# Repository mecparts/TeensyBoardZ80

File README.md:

# Teensy Board/Z80 - A Teensy4.0 based ZCPR3.3/ZSDOS Z80 computer

The Teensy Board/Z80 is a
[Teensy 4.0](https://www.pjrc.com/store/teensy40.html) computer running a
ZCPR3.3/ZSDOS variant of [RunCPM](https://github.com/MockbaTheBorg/RunCPM).

Features:
* 100-140MHz equivalent Z80 (RunCPM doesn't emulate cycle times - it just goes *fast*).
* SDIO connected uSD card (about 2.5x faster than SPI) with a standard FAT file system.
* ANSI colour terminal emulator with [GSX](https://github.com/mecparts/pigfx)
graphics support. Runs on a first generation Raspberry Pi, so HDMI video
and USB keyboards are natively supported.
* Battery backed up real time clock.
* Centronics compatible parallel port (DB-25F).
* RS-232 serial port (DE-9M) with RTS/CTS hardware flow control.

## Hardware

The PCB for the Teensy Board/Z80 fits on a VESA mount along with an
original Raspberry Pi 1 B (rev 2). The Pi is the ANSI console used by
the Teensy Board/Z80.

Along with the internal connection to the ANSI terminal, the Teensy Board/Z80
has two vintage I/O ports: an RS-232 port with a DE-9 connector, with
RTS/CTS handshaking, and a Centronics parallel port. The RS-232 port is
the TTY: device in the Teensy Board/Z80's BIOS. The parallel port is,
quite naturally, the LPT: device.

In my setup, the RS-232 port is hooked up to a
[Retro WiFi modem](https://github.com/mecparts/RetroWiFiModem), complete
with Hayes Smartmodem style LED indicators.

The Teensy 4's real time clock is used in ZSDOS to support file timestamps
via the normal ZSDOS calls. A CR2032 coin cell provides the battery back up.

## Case

The Ampro Little Board/Z80 mounted on the bottom of a 5.25" floppy drive.
The Teensy Board/Z80 mounts on a VESA mount on the back on an LCD monitor.

The case was designed in OpenSCAD. Although it's 3D printed, it's designed
like a laser cut case, with separate sides, top and bottom. This allowed
a quicker "getting it to fit" cycle than if the bottom and sides had been
printed as one piece; this way, individual sides could by reprinted.

The base is printed with integrated standoffs. The hole are sized to accept
a #4/40 tap so that no nuts are required. It took a bit of care to get the
holes tapped without snapping the standoffs. Both the Teensy Board PCB and
the Raspberry Pi will take 1/2" 4/40 screws in lieu of the M2.5s normally
specified for the Pi.

The sides bolt together with 3/8" #4-40 screws. The filament was plain old
PLA.

## Software

When I bought my first Teensy 4.0 last autumn, I'd thought about looking
around for a Z80 emulator written in C and implementing a BIOS in Z80
assembler that would talk to the Teensy hardware... somehow. Luckily, I
came across [RunCPM](https://github.com/MockbaTheBorg/RunCPM) first. It
had already solved the problem of communicating with the Teensy
hardware, and had done it with a FAT file system. I stopped looking! I
had the first system up and running within an hour of getting home with
the Teensy.

Over the winter I helped to get RunCPM's BDOS emulation much closer to
how CP/M operated. I'd done my fair share of BIOS development back in
the day, and had even done some work with a BDOS replacement called
*NovaDOS*, but all that was long ago and far away. But like riding a
bicycle, it all started coming back.

While all that was happening, I was also working on getting ZCPR3.3
working with RunCPM. Then, after adding proper serial and parallel port
support to RunCPM's BDOS and BIOS, I, well, started to get a little
carried away.

A couple of decades of having all those extra cursor and function keys
on my keyboard meant that I kept reaching for them. So I added the
equivalent a ZCPR3 IOP to RunCPM's console input handling. It handled
translating the ANSI style arrow, cursor and function keys to their
WordStar(tm) equivalents. Suddenly, *everything* that used the ZCPR TCAP
knew about all those extra keys. That was incredibly handy. Also, it took
no space at in the Z80's 64K.

The Teensy Board/Z80 also implements the GSX (Graphics System Extension)
BDOS call, but without the overhead of having GSX.SYS and a device
driver loaded in the TPA. No more GSX.SYS or GENGRAF.COM! Instead,
everything is handled in the Teensy Board/Z80's BDOS code. Most of the heavy
lifting actually occurs in my modified PiGFX code running on the
Raspberry Pi. Fast as a 115.2K serial connection is, it's way faster
sending the start and end point of a line and letting PiGFX draw it than
it would be to send a "set this pixel" command for each pixel in the
line.

Then, no longer satisfied with what NovaDOS did, I added ZSDOS
capabilities to RunCPM's BDOS. One of the most useful things to get
working was file datestamps. My favourite editor (ZDE16) was already
ZSDOS-aware and capable of maintaining the actual creation date of a
file; and its backup.

## Status

Newest working: ZMP has been re-compiled with Hi Tech C v3.09 and is
working. Baud rates above 19.2K now display properly (as do send/receive
times with at those speeds). Timestamps are working with Ymodem and
Zmodem. Keyboard macros now send CR for ! rather than CR/LF. Automatic
CR on connection has been removed. ! and ~ can be escaped with \ in
keyboard macros so those characters can be sent.

## References

* [RunCPM](https://github.com/MockbaTheBorg/RunCPM): the original
inspiration for this whole project. While RunCPM may not have been
intended to emulate a complete CP/M computer, as the Teensy Board/Z80
shows there's no reason that it can't be expanded into one.
* [PiGFX](https://github.com/mecparts/pigfx): a fork of 
https://github.com/dhansel/pigfx (which is a fork of 
https://github.com/fbergama/pigfx) with all kinds of additions, including
native GSX support.
* [SdFat-beta](https://github.com/mecparts/SdFat-beta): a fork of
https://github.com/greiman/SdFat-beta with support for file attributes.
* [Retro WiFi Modem](https://github.com/mecparts/RetroWiFiModem): a 
WiFi modem in the style of an old Hayes Smartmodem. True RS-232 interface
and LED status indicators.

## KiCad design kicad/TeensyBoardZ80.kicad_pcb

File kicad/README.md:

# Teensy Board/Z80 - A Teensy4.0 based ZCPR3.3/ZSDOS Z80 computer

## Schematic

I've been asked "why didn't you use a Teensy 4.1 with the built in uSD
holder?" The simple answer is that I designed this before the 4.1 was
announced.

And as to why all the thru hole parts were used when surface mount 
would have allowed either a smaller board or more features in the same
amount of space, this was a "use as many parts that I actually have on
hand" project.

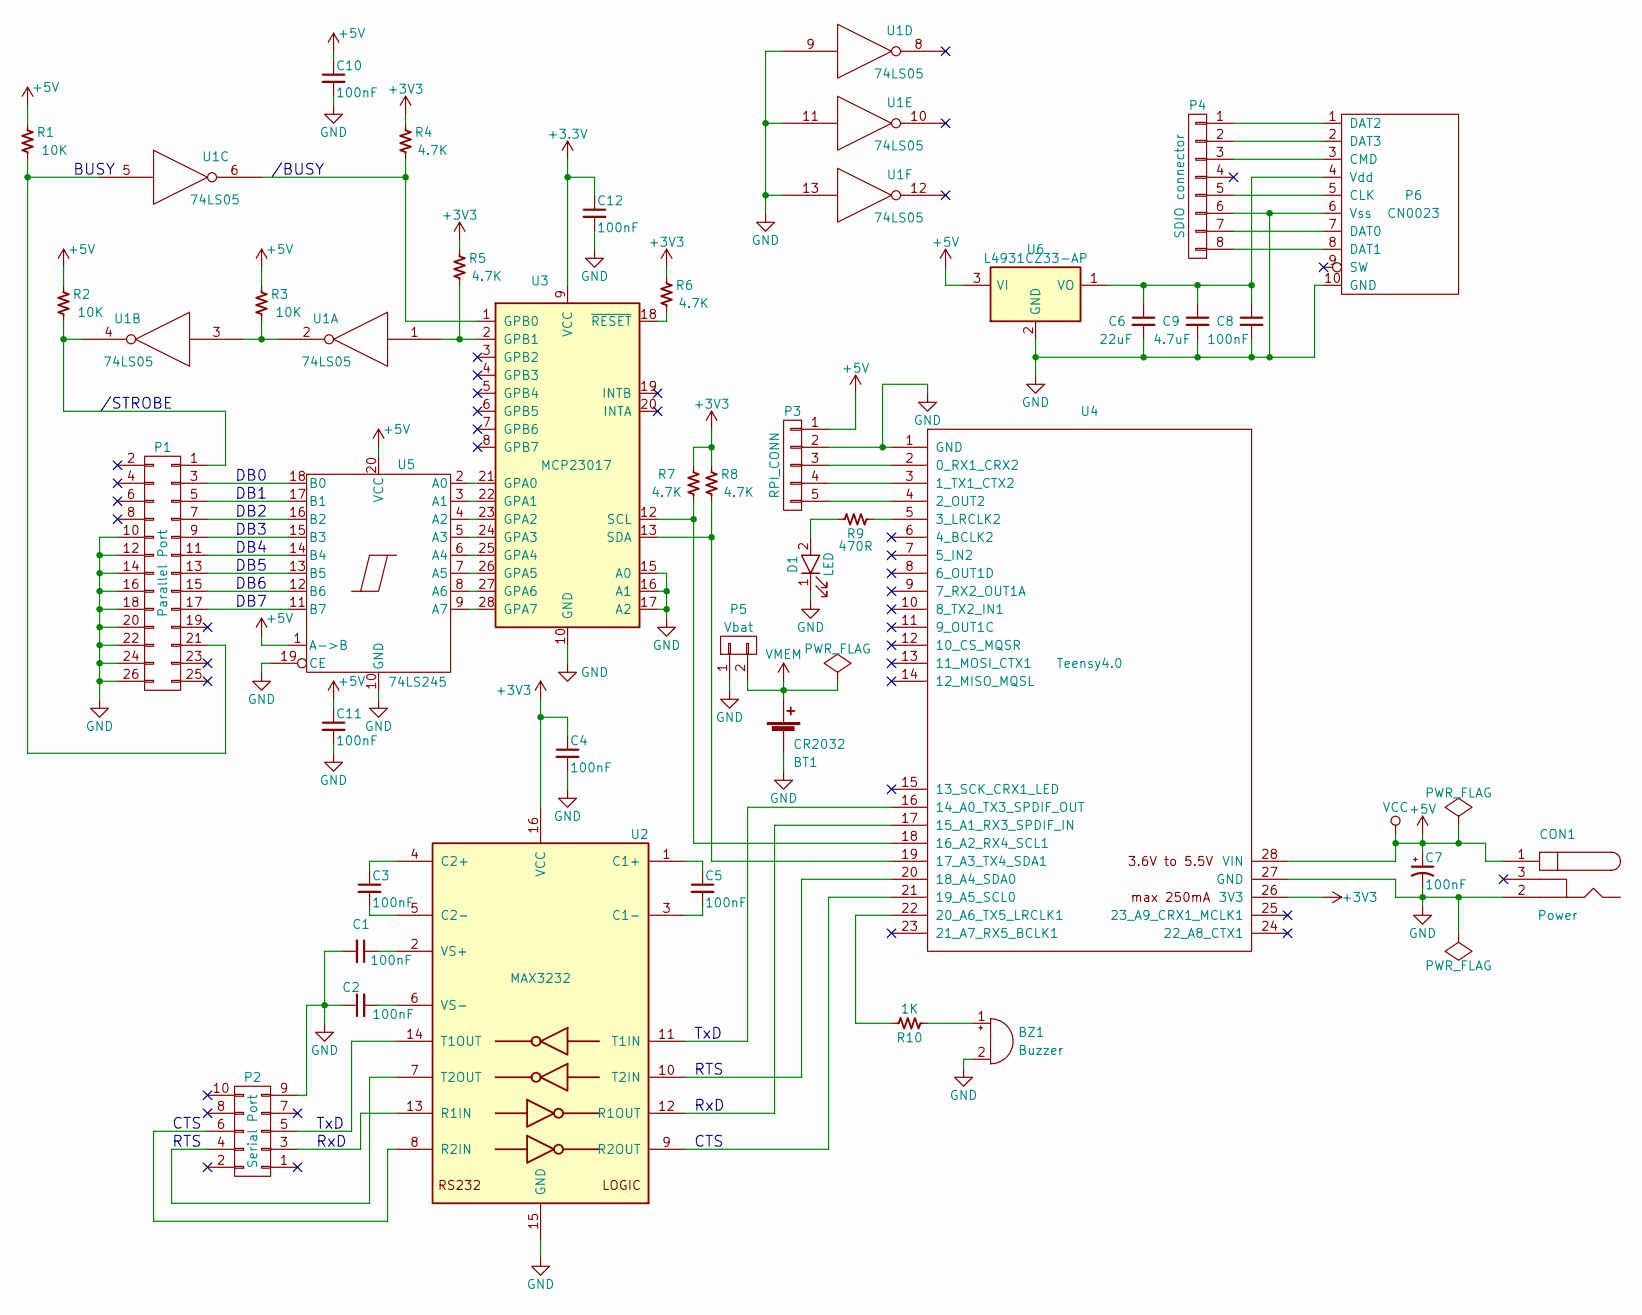
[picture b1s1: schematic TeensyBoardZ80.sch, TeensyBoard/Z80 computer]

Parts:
BT1: CR2032; CR2032V; DigiKey PN BS-5-ND
BZ1: Buzzer; PKM22EPP; DigiKey PN 490-7031-ND
C1, C2, C3, C4, C7, C8, C10, C11, C12: 100nF; C_Disc_D3_P2.5; DigiKey PN 399-9843-ND
C5: 100nF; C_Axial_D2.5_L4.3_P7.5; DigiKey PN 399-9843-ND
C6: 22uF; C_Disc_D3_P2.5; DigiKey PN 399-3574-ND
C9: 4.7uF; C_Disc_D3_P2.5; DigiKey PN 399-3543-ND
CON1: Power; BARREL_JACK; DigiKey PN 839-54-00166-ND
D1: LED; Pin_Header_Straight_1x02
P1: Parallel Port; IDC_Header_Straight_26pins; DigiKey PN 377-2269-ND
P2: Serial Port; IDC_Header_Straight_10pins; DigiKey PN 296-1589-5-ND
P3: RPI_CONN; Pin_Header_Straight_1x05
P4: SDIO connector; HLW8R-2C7LF; DigiKey PN HLW8R-2C7LF
P5: Vbat; Pin_Header_Straight_1x02
P6: CN0023; DigiKey PN CN0023-ND
R1, R2, R3: 10K; R3; DigiKey PN CF18JT10K0CT-ND
R4, R5, R6, R7, R8: 4.7K; R3; DigiKey PN CF18JT4K70CT-ND
R9: 470R; R3; DigiKey PN CF18JT470R
R10: 1K; R3; DigiKey PN CF18JT1K00CT-ND
U1: 74LS05; DIP-14_W7.62mm_LongPads; DigiKey PN 296-1631-5-ND
U2: MAX3232; DIP-16_W7.62mm; DigiKey PN ICL3232CPZ-ND
U3: MCP23017; DIP-28_W7.62mm_LongPads
U4: Teensy4.0; Teensy40; DigiKey PN 1568-DEV-15583-ND
U5: 74LS245; DIP-20_W7.62mm_LongPads
U6: L4931CZ33-AP; TO-92_Inline_Wide; DigiKey PN 497-7246-1-ND

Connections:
+5V: C7.1, C10.1, C11.1, CON1.1, P3.1, R1.2, R2.2, R3.2, U1.14 (VCC), U4.28 (VIN), U5.1 (A->B), U5.20 (VCC), U6.3 (VI)
GND: BT1.2 (-), BZ1.2 (+), C1.2, C2.1, C4.2, C6.2, C7.2, C8.2, C9.2, C10.2, C11.2, C12.2, CON1.2, D1.1 (K), P1.10, P1.12, P1.14, P1.16, P1.18, P1.20, P1.22, P1.24, P1.26, P2.9, P3.2, P4.6, P5.1, P6.6 (Vss), P6.10 (GND), U1.7 (GND), U1.9, U1.11, U1.13, U2.15 (GND), U3.10 (GND), U3.15 (A0), U3.16 (A1), U3.17 (A2), U4.1 (GND), U4.27 (GND), U5.10 (GND), U5.19 (CE), U6.2 (GND)
unnamed: BZ1.1 (-), R10.1
unnamed: C1.1, U2.2 (VS+)
unnamed: C2.2, U2.6 (VS-)
unnamed: C3.1, U2.4 (C2+)
unnamed: C3.2, U2.5 (C2-)
unnamed: C5.1, U2.1 (C1+)
unnamed: C5.2, U2.3 (C1-)
unnamed: C6.1, C8.1, C9.1, P6.4 (Vdd), U6.1 (VO)
unnamed: D1.2 (A), R9.2
unnamed: P1.1, R2.1, U1.4
unnamed: P1.3, U5.18 (B0)
unnamed: P1.5, U5.17 (B1)
unnamed: P1.7, U5.16 (B2)
unnamed: P1.9, U5.15 (B3)
unnamed: P1.11, U5.14 (B4)
unnamed: P1.13, U5.13 (B5)
unnamed: P1.15, U5.12 (B6)
unnamed: P1.17, U5.11 (B7)
unnamed: P1.21, R1.1, U1.5
unnamed: P2.3, U2.13 (R1IN)
unnamed: P2.4, U2.7 (T2OUT)
unnamed: P2.5, U2.14 (T1OUT)
unnamed: P2.6, U2.8 (R2IN)
unnamed: P3.3, U4.2 (0_RX1_CRX2)
unnamed: P3.4, U4.3 (1_TX1_CTX2)
unnamed: P3.5, U4.4 (2_OUT2)
unnamed: P4.1, P6.1 (DAT2)
unnamed: P4.2, P6.2 (DAT3)
unnamed: P4.3, P6.3 (CMD)
unnamed: P4.5, P6.5 (CLK)
unnamed: P4.7, P6.7 (DAT0)
unnamed: P4.8, P6.8 (DAT1)
unnamed: R3.1, U1.2, U1.3
unnamed: R4.1, U1.6, U3.1 (GPB0)
unnamed: R5.1, U1.1, U3.2 (GPB1)
unnamed: R6.1, U3.18 (~RESET)
unnamed: R7.1, U3.12 (SCL), U4.18 (16_A2_RX4_SCL1)
unnamed: R8.1, U3.13 (SDA), U4.19 (17_A3_TX4_SDA1)
unnamed: R9.1, U4.5 (3_LRCLK2)
unnamed: R10.2, U4.22 (20_A6_TX5_LRCLK1)
unnamed: U2.9 (R2OUT), U4.21 (19_A5_SCL0)
unnamed: U2.10 (T2IN), U4.20 (18_A4_SDA0)
unnamed: U2.11 (T1IN), U4.16 (14_A0_TX3_SPDIF_OUT)
unnamed: U2.12 (R1OUT), U4.17 (15_A1_RX3_SPDIF_IN)
unnamed: U3.21 (GPA0), U5.2 (A0)
unnamed: U3.22 (GPA1), U5.3 (A1)
unnamed: U3.23 (GPA2), U5.4 (A2)
unnamed: U3.24 (GPA3), U5.5 (A3)
unnamed: U3.25 (GPA4), U5.6 (A4)
unnamed: U3.26 (GPA5), U5.7 (A5)
unnamed: U3.27 (GPA6), U5.8 (A6)
unnamed: U3.28 (GPA7), U5.9 (A7)
VMEM: BT1.1 (+), P5.2

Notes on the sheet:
BUSY
/BUSY
TxD
RTS
RxD
CTS
/STROBE
DB7
DB6
DB5
DB4
DB3
DB2
DB1
DB0

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
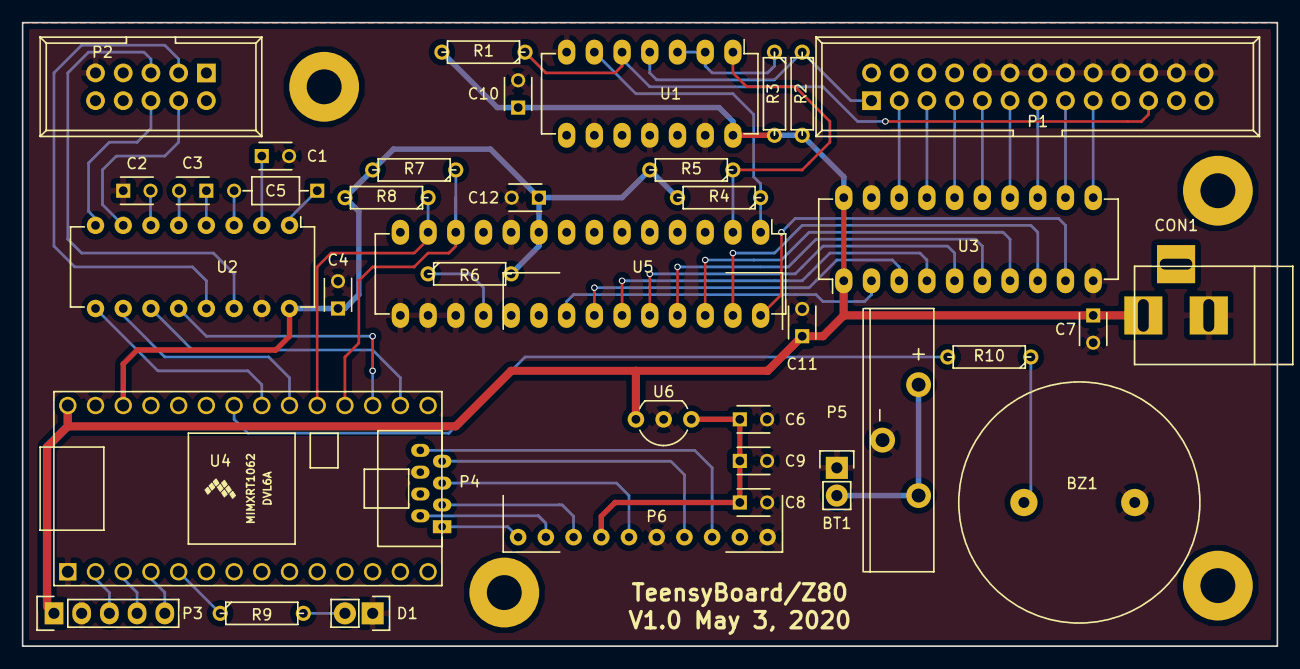
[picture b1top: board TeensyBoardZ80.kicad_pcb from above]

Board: 2 copper layers, 115.0 x 57.2 mm, 38 parts (0 on the bottom side), 56 nets.

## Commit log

2020-06-24 Missed a ! in the readme file.
2020-06-24 Added image text
2020-06-24 First of what I expect will be many spelling mistakes.
2020-06-24 Added kicad files
2020-06-24 More spelling oops.
2020-06-24 Removed unneeded file
2020-06-24 More README tweaks.
2020-06-24 Adding COM & HLP files to disk image
2020-06-24 Add some source and documentation files
2020-06-24 Added schematic image
2020-06-24 Correct schematic image link
2020-06-24 Removed a superfluous file
2020-06-24 Added the STL file for the VESA mount base
2020-06-25 Moved WiFi specific baud rate change code out of BIOS and into ZMP overlay so that serial port can be used for other things as well.
2020-06-25 New overlay for ZMP that also sets the WiFi modem serial speed
2020-06-25 Removed old ZMP overlay (git got confused if I tried to add the new one and remove the old one in one commit)
2020-07-05 Updated README.md to current status.
2020-07-22 Added missing PCB files
2020-07-22 BDOS call 105/200: return BCD seconds in A to emulate MP/M II behaviour for HiTech C v3.09
2020-07-23 Updated ZMP files with new version compiled with Hi Tech C v3.09 from http://github.com/mecparts/zmp
2020-07-23 Updated README.md to reflect new ZMP version.
2020-07-25 Updated work status in README.md
2020-07-26 Updated ZMP to latest version.
2020-08-03 1. Added .gitignore. 2. First cut at request/response GSX calls.
2020-08-10 Updated ZMTERM and ZMCONFIG overlays to newest versions.
2020-08-11 Patched RTS lockout on baud rate change When dialing a number in ZMP, if I aborted the dial once every so often the RTS line would go inactive and stay that way. It could only be fixed by doing a reb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
2020-08-12 Updated ZMP overlay files to newest version
2020-09-20 Updated ZMTERM.OVR to latest version
2020-10-07 Added CPA utility to disk image.
2020-10-17 Added P2DOS timestamp to dir buffer returned by find first/next Though ZSDOS included ZXD.COM, ZXD didn't use the ZSDOS calls to get the file's timestamp, instead it went to the data in the directory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
2020-10-20 BIOS SELDSK call now returns a sensible DPH Previously, this call always returned a 0 in HL, signalling that the drive did not exist. ZCPR3's FF.COM used this call to figure out whether a drive exist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
2020-10-20 Public file support for find first/next BDOS calls In order to get DazzleStar (a disassembler) to play nicely with user areas, it was necessary to add public file support to the find first/next BDOS 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
2020-10-26 A quick hack to make F1 and F2 type the current date and time Ugly code getting uglier but hey, it works.
2020-11-07 Moved most of the ANSI -> WordStar translation to PiGFX.
2020-11-07 Updated ZMP.COM to latest version
2020-11-07 Added source code of latest Teensy Board/Z80 ZMP overlay.
2020-11-07 Removed ESC doubling in 8 bit input mode Now that I've been able to recompile ZMP, I was able to modify it to allow ANSI cursor sequences from the keyboard to pass thru (by checking to see if there w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
2020-11-07 Updated ZMTERM.OVR to handle ANSI cursor/func keys
2020-11-23 Expanded I/O byte support Added support for the USB serial port as physical devices UC1, UR1, UP1 (user console 1, user reader 1, user punch 1). Also added support for the logical device BAT (RDR in,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
2021-03-22 Updated ZMCONFIG.OVR to latest version
2021-06-07 Updated ZMP to latest bug fix (long filename conversion error on X/YModem receive)
2021-06-10 Moved SO/SI check from _putcrt to _putcon so that 8 bit output flag would be honoured for all logical console devices, not just the physical CRT device.
2021-06-10 Added a lock bit to the NovaDos flags byte so that ZMP would have a mechanism to lock 8 bit output on for the duration it was running, and remote systems (I'm looking at you, Particles! BBS) wouldn't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
2021-06-11 Latest version of ZMP.COM and ZMP overlay files.
2021-06-13 Added a .gitattributes file
2021-06-13 Updated .gitattribtues file
2021-06-13 Another try at getting .gitattributes right!
2021-06-13 One last try at getting .gitattributes right
2021-09-20 1. Moved serial port initialisation before 3 second startup wait. 2. Changed TTY startup baud from 1200 to 9600. 3. Initialised MSPEED variable. 4. Routed CTS signal to a spare input pin so I could r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
2021-10-07 Changed ZCPR3 clear & home to <ESC>[H<ESC>[J for PuTTY
2021-10-07 Don't mask off high bit in BIOS CONOUT (_putcon already does this)
2023-08-04 When RTS/CTS flow control is turned off, disable the CTS pin.
2023-08-04 Fixed a bug in the phone number list editor. 38400, 57600 and 76800 couldn't be selected because the code was using atoi() rather than atol().
2023-08-12 Update ZMTERM.OVR to latest version
2023-08-15 Update to latest ZMP version.
